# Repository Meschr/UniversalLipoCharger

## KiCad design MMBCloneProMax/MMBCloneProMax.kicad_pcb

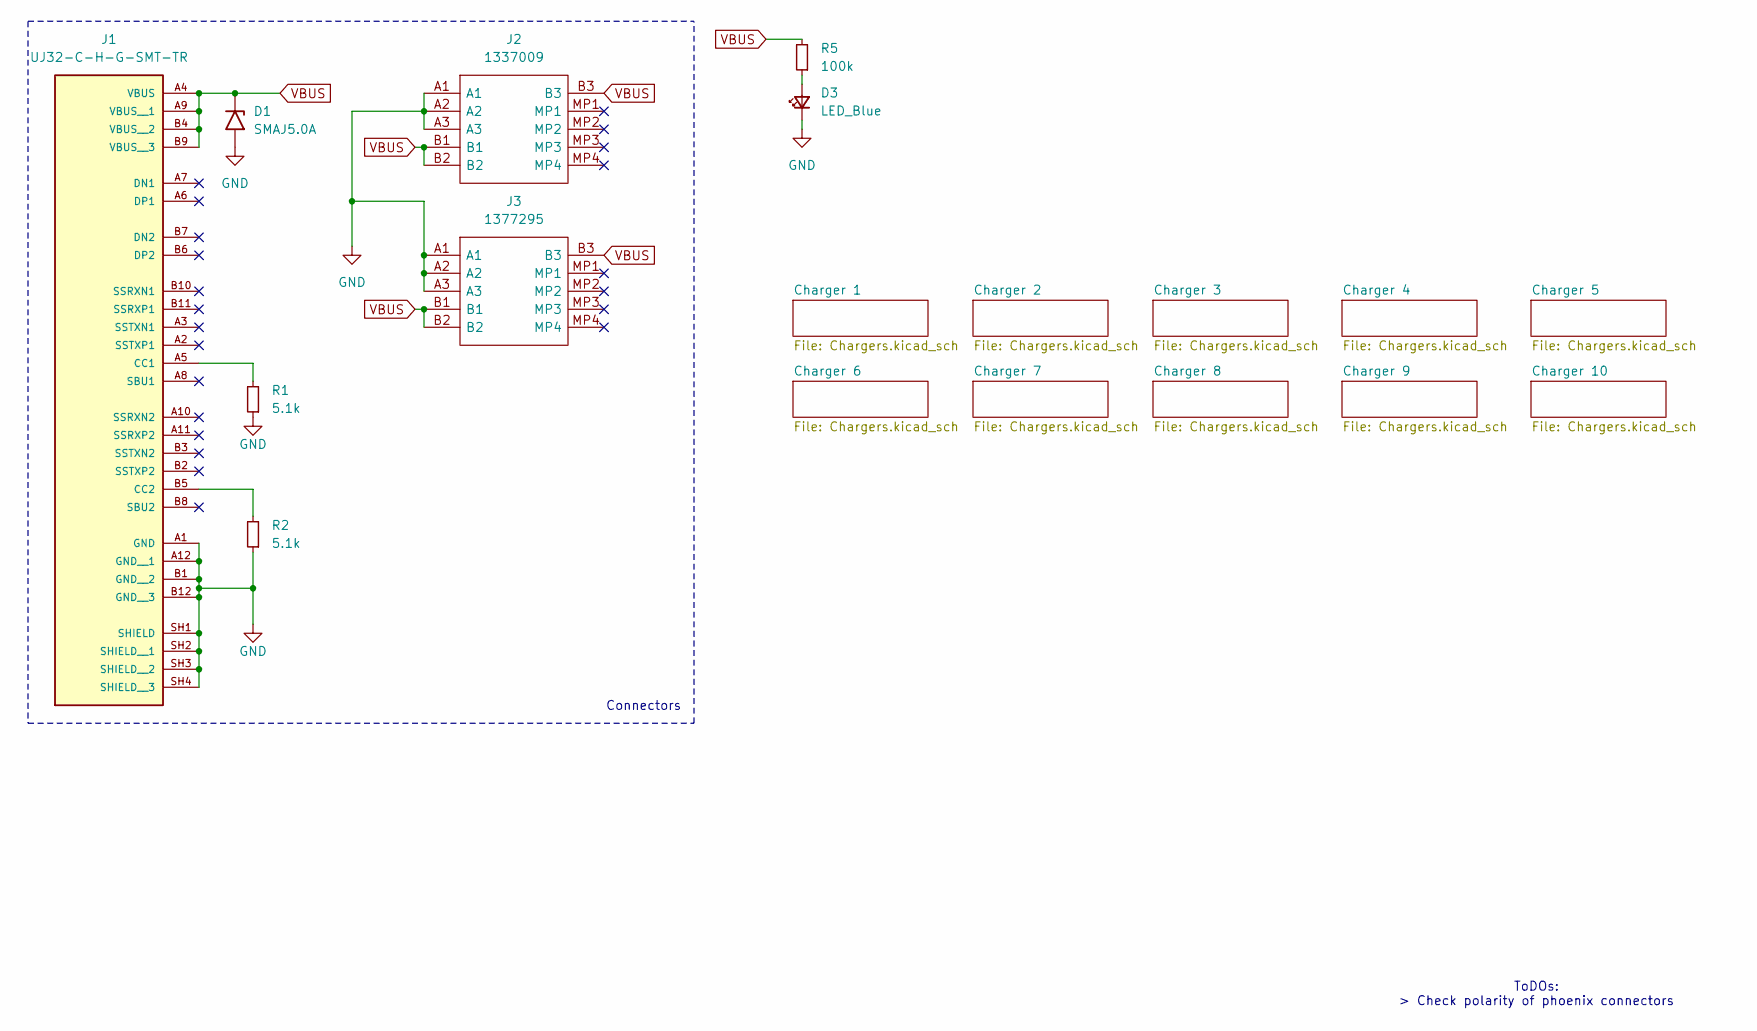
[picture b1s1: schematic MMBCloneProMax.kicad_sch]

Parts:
D1: SMAJ5.0A; D_SMA
D3: LED_Blue; LED_0603_1608Metric
J1: UJ32-C-H-G-SMT-TR; CUI_UJ32-C-H-G-SMT-TR; PARTREV 1.01
J2: 1337009; Mouser Part Number 651-1337009
J3: 1377295; Mouser Part Number 651-1377295
R1, R2: 5.1k; R_0603_1608Metric
R5: 100k; R_0603_1608Metric

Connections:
GND: D1.2 (A2), D3.1 (K), J1.A1 (GND), J1.A12 (GND__1), J1.B1 (GND__2), J1.B12 (GND__3), J1.SH1 (SHIELD), J1.SH2 (SHIELD__1), J1.SH3 (SHIELD__2), J1.SH4 (SHIELD__3), J2.A1, J2.A2, J2.A3, J3.A1, J3.A2, J3.A3, R1.1, R2.1; also elsewhere on the board
unnamed: D3.2 (A), R5.1
unnamed: J1.A5 (CC1), R1.2
unnamed: J1.B5 (CC2), R2.2
VBUS: D1.1 (A1), J1.A4 (VBUS), J1.A9 (VBUS__1), J1.B4 (VBUS__2), J1.B9 (VBUS__3), J2.B1, J2.B2, J2.B3, J3.B1, J3.B2, J3.B3, R5.2; also elsewhere on the board

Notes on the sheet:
Connectors
ToDOs: > Check polarity of phoenix connectors

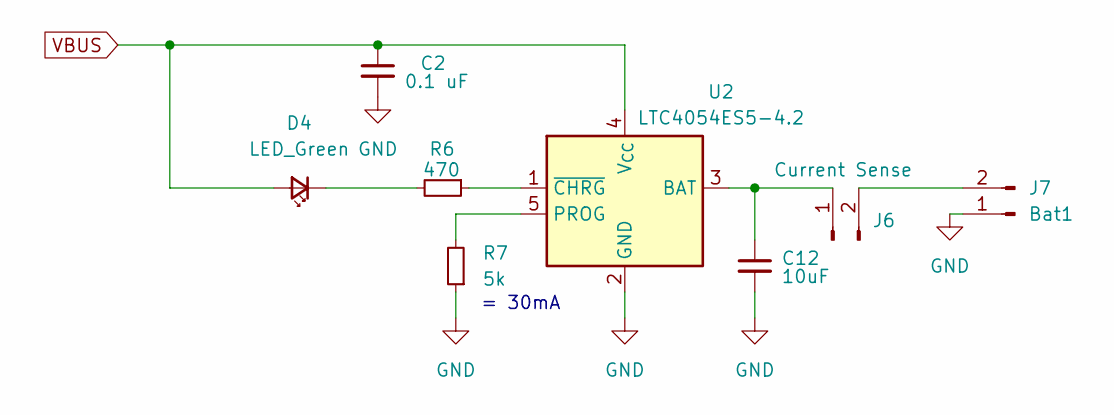
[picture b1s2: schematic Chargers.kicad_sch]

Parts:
C2: 0.1 uF; C_0603_1608Metric
C12: 10uF; C_0603_1608Metric
D4: LED_Green; LED_0603_1608Metric
J6: Current Sense; PinHeader_1x02_P2.54mm_Vertical
J7: Bat1; SHDR2W64P0X254_1X2_508X580X1170P
R6: 470; R_0603_1608Metric
R7: 5k; C_0603_1608Metric
U2: LTC4054ES5-4.2; TSOT-23-5

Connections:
GND: C2.2, C12.2, J7.1, R7.1, U2.2 (GND); also elsewhere on the board
unnamed: D4.1 (K), R6.2
unnamed: C12.1, J6.1, U2.3 (BAT)
unnamed: J6.2, J7.2
unnamed: R7.2, U2.5 (PROG)
unnamed: R6.1, U2.1 (~CHRG)
VBUS: C2.1, D4.2 (A), U2.4 (V_{CC}); also elsewhere on the board

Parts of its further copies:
C1, C3, C4, C5, C6, C7, C8, C9, C10: 0.1 uF; C_0603_1608Metric
C11, C13, C14, C15, C16, C17, C18, C19, C20: 10uF; C_0603_1608Metric
D2, D5, D6, D7, D8, D9, D10, D11, D12: LED_Green; LED_0603_1608Metric
J4, J8, J10, J12, J14, J16, J18, J20, J22: Current Sense; PinHeader_1x02_P2.54mm_Vertical
J5, J9, J11, J13, J15, J17, J19, J21, J23: Bat1; SHDR2W64P0X254_1X2_508X580X1170P
R3, R8, R10, R12, R14, R16, R18, R20, R22: 470; R_0603_1608Metric
R4, R9, R11, R13, R15, R17, R19, R21, R23: 5k; C_0603_1608Metric
U1, U3, U4, U5, U6, U7, U8, U9, U10: LTC4054ES5-4.2; TSOT-23-5

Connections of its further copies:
GND: C1.2, C3.2, C4.2, C5.2, C6.2, C7.2, C8.2, C9.2, C10.2, C11.2, C13.2, C14.2, C15.2, C16.2, C17.2, C18.2, C19.2, C20.2, J5.1, J9.1, J11.1, J13.1, J15.1, J17.1, J19.1, J21.1, J23.1, R4.1, R9.1, R11.1, R13.1, R15.1, R17.1, R19.1, R21.1, R23.1, U1.2 (GND), U3.2 (GND), U4.2 (GND), U5.2 (GND), U6.2 (GND), U7.2 (GND), U8.2 (GND), U9.2 (GND), U10.2 (GND); also elsewhere on the board
unnamed: D2.1 (K), R3.2
unnamed: D5.1 (K), R8.2
unnamed: D6.1 (K), R10.2
unnamed: D7.1 (K), R12.2
unnamed: D8.1 (K), R14.2
unnamed: D9.1 (K), R16.2
unnamed: D10.1 (K), R18.2
unnamed: D11.1 (K), R20.2
unnamed: D12.1 (K), R22.2
unnamed: C11.1, J4.1, U1.3 (BAT)
unnamed: J4.2, J5.2
unnamed: C13.1, J8.1, U3.3 (BAT)
unnamed: J8.2, J9.2
unnamed: C14.1, J10.1, U4.3 (BAT)
unnamed: J10.2, J11.2
unnamed: C15.1, J12.1, U5.3 (BAT)
unnamed: J12.2, J13.2
unnamed: C16.1, J14.1, U6.3 (BAT)
unnamed: J14.2, J15.2
unnamed: C17.1, J16.1, U7.3 (BAT)
unnamed: J16.2, J17.2
unnamed: C18.1, J18.1, U8.3 (BAT)
unnamed: J18.2, J19.2
unnamed: C19.1, J20.1, U9.3 (BAT)
unnamed: J20.2, J21.2
unnamed: C20.1, J22.1, U10.3 (BAT)
unnamed: J22.2, J23.2
unnamed: R4.2, U1.5 (PROG)
unnamed: R3.1, U1.1 (~CHRG)
unnamed: R9.2, U3.5 (PROG)
unnamed: R8.1, U3.1 (~CHRG)
unnamed: R11.2, U4.5 (PROG)
unnamed: R10.1, U4.1 (~CHRG)
unnamed: R13.2, U5.5 (PROG)
unnamed: R12.1, U5.1 (~CHRG)
unnamed: R15.2, U6.5 (PROG)
unnamed: R14.1, U6.1 (~CHRG)
unnamed: R17.2, U7.5 (PROG)
unnamed: R16.1, U7.1 (~CHRG)
unnamed: R19.2, U8.5 (PROG)
unnamed: R18.1, U8.1 (~CHRG)
unnamed: R21.2, U9.5 (PROG)
unnamed: R20.1, U9.1 (~CHRG)
unnamed: R23.2, U10.5 (PROG)
unnamed: R22.1, U10.1 (~CHRG)
VBUS: C1.1, C3.1, C4.1, C5.1, C6.1, C7.1, C8.1, C9.1, C10.1, D2.2 (A), D5.2 (A), D6.2 (A), D7.2 (A), D8.2 (A), D9.2 (A), D10.2 (A), D11.2 (A), D12.2 (A), U1.4 (V_{CC}), U3.4 (V_{CC}), U4.4 (V_{CC}), U5.4 (V_{CC}), U6.4 (V_{CC}), U7.4 (V_{CC}), U8.4 (V_{CC}), U9.4 (V_{CC}), U10.4 (V_{CC}); also elsewhere on the board

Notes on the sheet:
= 30mA

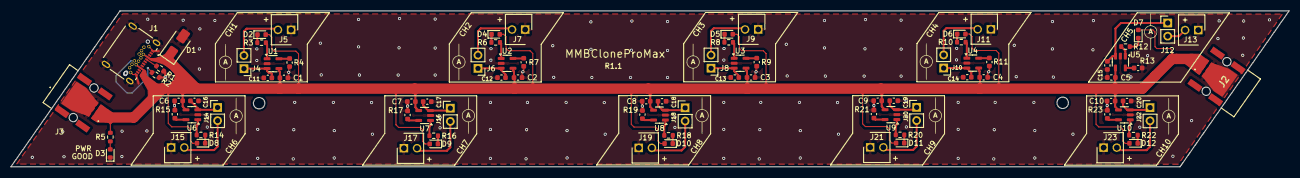
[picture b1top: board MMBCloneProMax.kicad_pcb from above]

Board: 2 copper layers, 246.2 x 30.0 mm, 88 parts (0 on the bottom side), 55 nets.

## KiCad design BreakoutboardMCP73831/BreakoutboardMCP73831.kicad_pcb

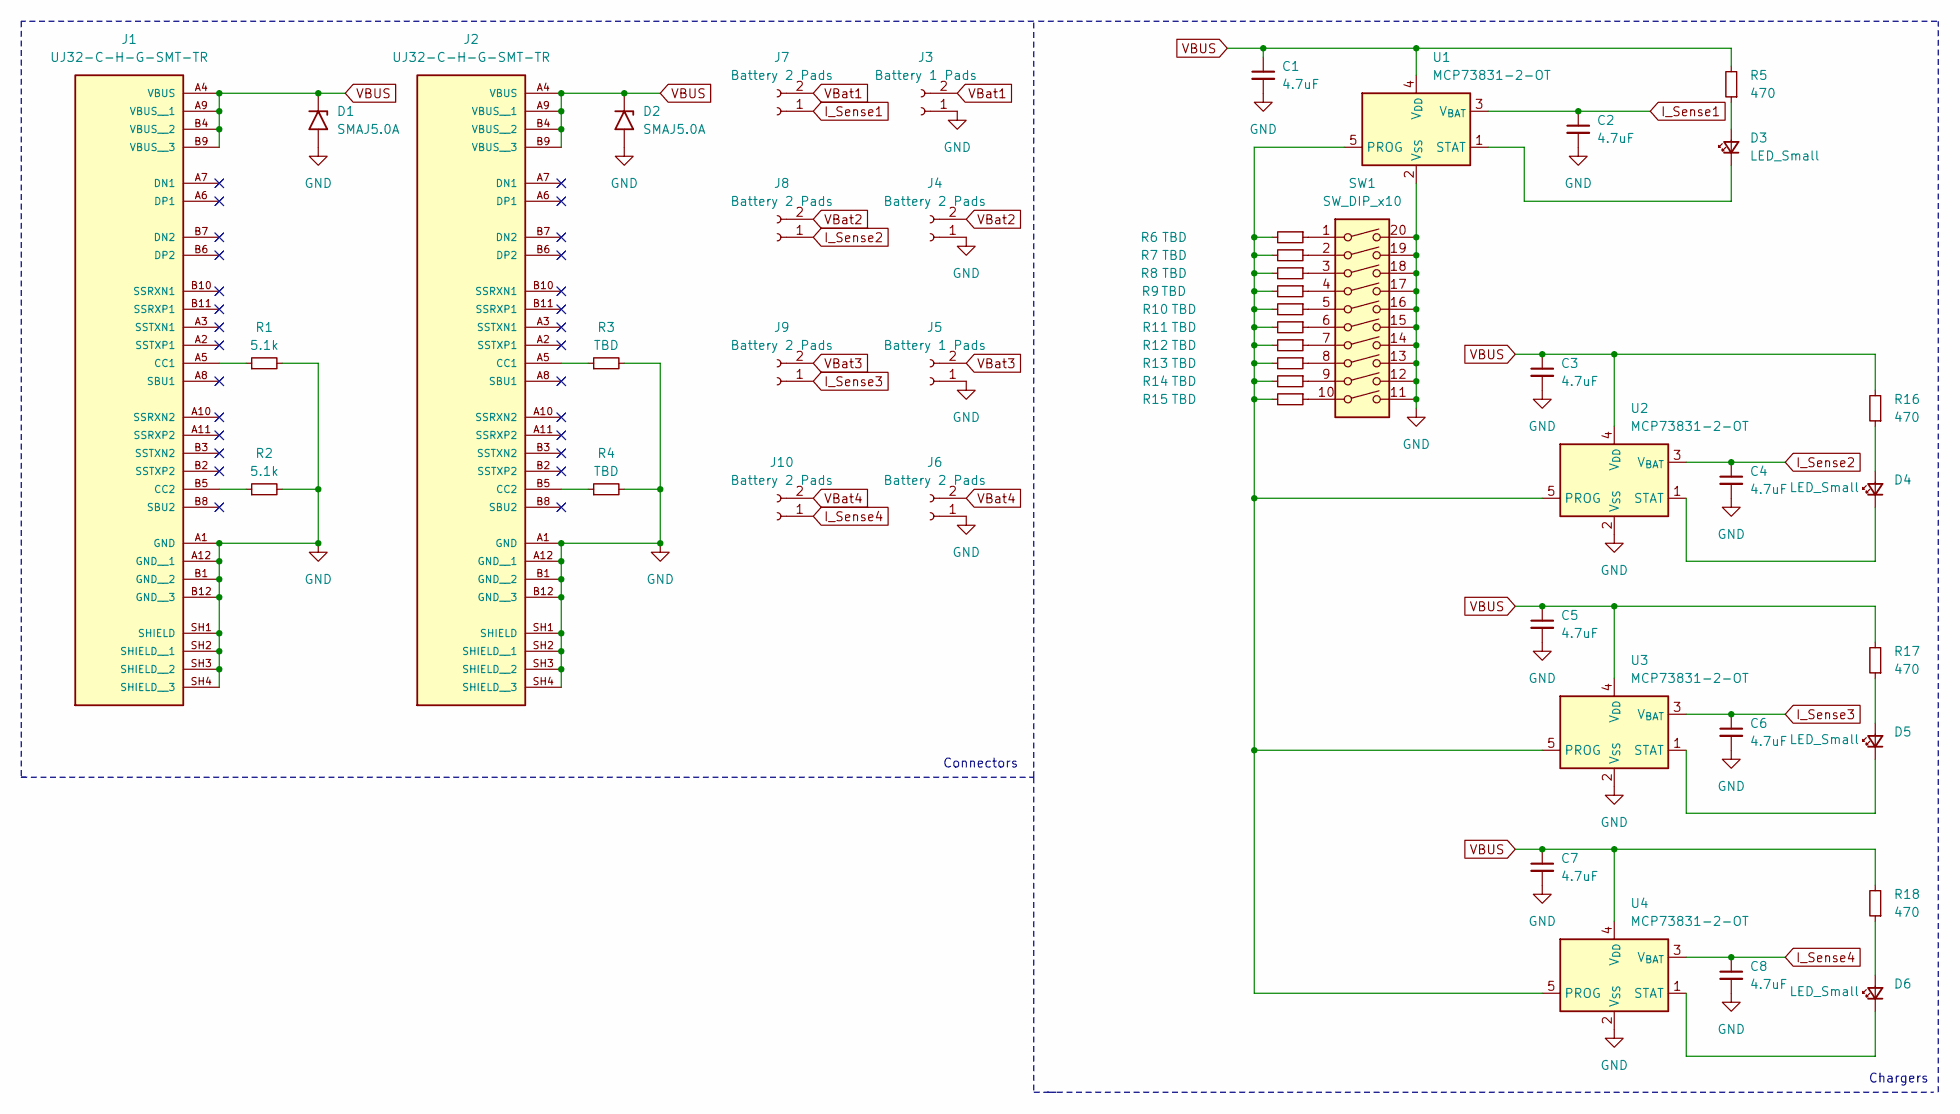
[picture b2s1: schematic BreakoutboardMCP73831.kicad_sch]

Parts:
C1, C2, C3, C4, C5, C6, C7, C8: 4.7uF; C_0402_1005Metric
D1, D2: SMAJ5.0A; D_SMA
D3, D4, D5, D6: LED_Small; LED_0402_1005Metric
J1, J2: UJ32-C-H-G-SMT-TR; CUI_UJ32-C-H-G-SMT-TR; PARTREV 1.01
J3, J5: Battery 1 Pads; PinHeader_1x02_P2.54mm_Vertical
J4, J6, J7, J8, J9, J10: Battery 2 Pads; PinHeader_1x02_P2.54mm_Vertical
R1, R2: 5.1k; R_0402_1005Metric
R3, R4, R6, R7, R8, R9, R10, R11, R12, R13, R14, R15: TBD; R_0402_1005Metric
R5, R16, R17, R18: 470; R_0402_1005Metric
SW1: SW_DIP_x10; SW_DIP_SPSTx10_Slide_6.7x26.96mm_W6.73mm_P2.54mm_LowProfile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
U1, U2, U3, U4: MCP73831-2-OT; SOT-23-5

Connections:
GND: C1.2, C2.2, C3.2, C4.2, C5.2, C6.2, C7.2, C8.2, D1.2 (A2), D2.2 (A2), J1.A1 (GND), J1.A12 (GND__1), J1.B1 (GND__2), J1.B12 (GND__3), J1.SH1 (SHIELD), J1.SH2 (SHIELD__1), J1.SH3 (SHIELD__2), J1.SH4 (SHIELD__3), J2.A1 (GND), J2.A12 (GND__1), J2.B1 (GND__2), J2.B12 (GND__3), J2.SH1 (SHIELD), J2.SH2 (SHIELD__1), J2.SH3 (SHIELD__2), J2.SH4 (SHIELD__3), J3.1, J4.1, J5.1, J6.1, R1.2, R2.2, R3.2, R4.2, SW1.11, SW1.12, SW1.13, SW1.14, SW1.15, SW1.16, SW1.17, SW1.18, SW1.19, SW1.20, U1.2 (V_{SS}), U2.2 (V_{SS}), U3.2 (V_{SS}), U4.2 (V_{SS})
I_Sense1: C2.1, J7.1, U1.3 (V_{BAT})
I_Sense2: C4.1, J8.1, U2.3 (V_{BAT})
I_Sense3: C6.1, J9.1, U3.3 (V_{BAT})
I_Sense4: C8.1, J10.1, U4.3 (V_{BAT})
unnamed: D3.2 (A), R5.1
unnamed: D3.1 (K), U1.1 (STAT)
unnamed: D4.2 (A), R16.1
unnamed: D4.1 (K), U2.1 (STAT)
unnamed: D5.2 (A), R17.1
unnamed: D5.1 (K), U3.1 (STAT)
unnamed: D6.2 (A), R18.1
unnamed: D6.1 (K), U4.1 (STAT)
unnamed: J1.A5 (CC1), R1.1
unnamed: J1.B5 (CC2), R2.1
unnamed: J2.A5 (CC1), R3.1
unnamed: J2.B5 (CC2), R4.1
unnamed: R6.1, SW1.1
unnamed: R7.1, SW1.2
unnamed: R8.1, SW1.3
unnamed: R9.1, SW1.4
unnamed: R10.1, SW1.5
unnamed: R11.1, SW1.6
unnamed: R12.1, SW1.7
unnamed: R13.1, SW1.8
unnamed: R14.1, SW1.9
unnamed: R15.1, SW1.10
unnamed: R6.2, R7.2, R8.2, R9.2, R10.2, R11.2, R12.2, R13.2, R14.2, R15.2, U1.5 (PROG), U2.5 (PROG), U3.5 (PROG), U4.5 (PROG)
VBUS: C1.1, C3.1, C5.1, C7.1, D1.1 (A1), D2.1 (A1), J1.A4 (VBUS), J1.A9 (VBUS__1), J1.B4 (VBUS__2), J1.B9 (VBUS__3), J2.A4 (VBUS), J2.A9 (VBUS__1), J2.B4 (VBUS__2), J2.B9 (VBUS__3), R5.2, R16.2, R17.2, R18.2, U1.4 (V_{DD}), U2.4 (V_{DD}), U3.4 (V_{DD}), U4.4 (V_{DD})
VBat1: J3.2, J7.2
VBat2: J4.2, J8.2
VBat3: J5.2, J9.2
VBat4: J6.2, J10.2

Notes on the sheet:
Chargers
Connectors

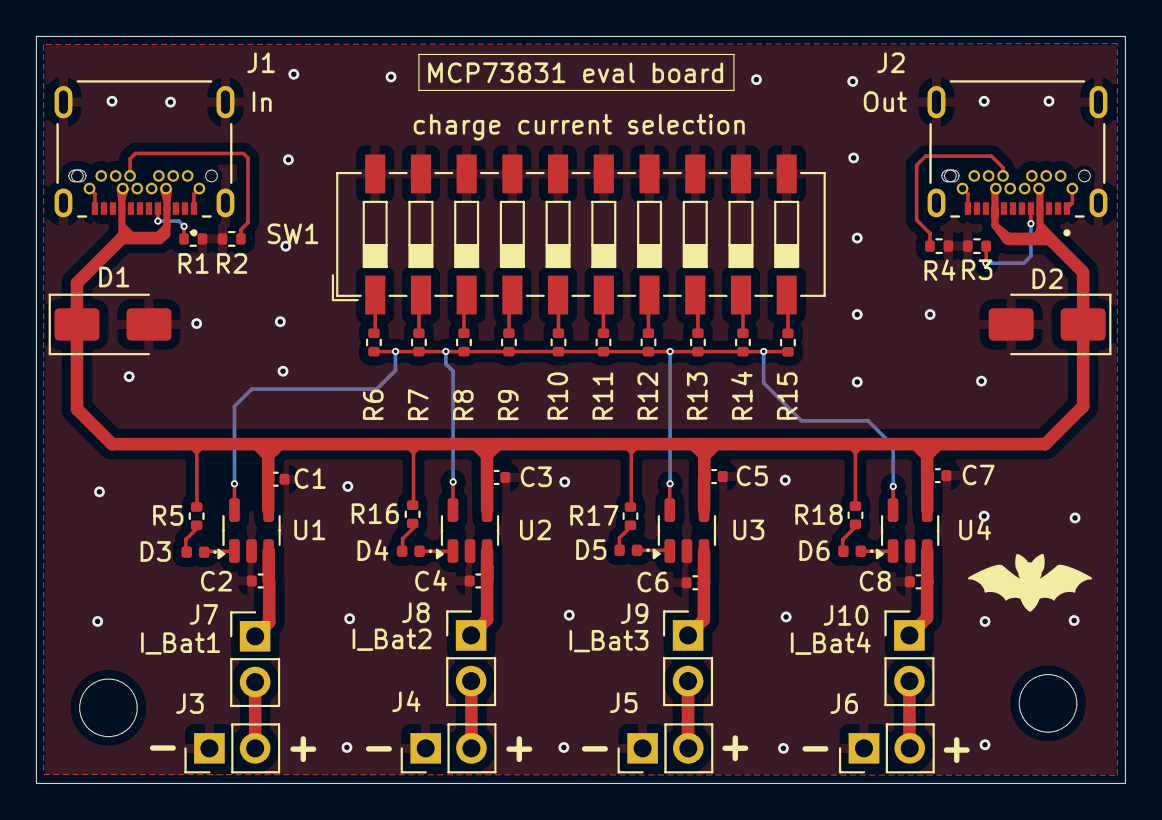
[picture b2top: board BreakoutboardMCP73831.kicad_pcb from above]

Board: 2 copper layers, 60.5 x 41.5 mm, 47 parts (0 on the bottom side), 33 nets.

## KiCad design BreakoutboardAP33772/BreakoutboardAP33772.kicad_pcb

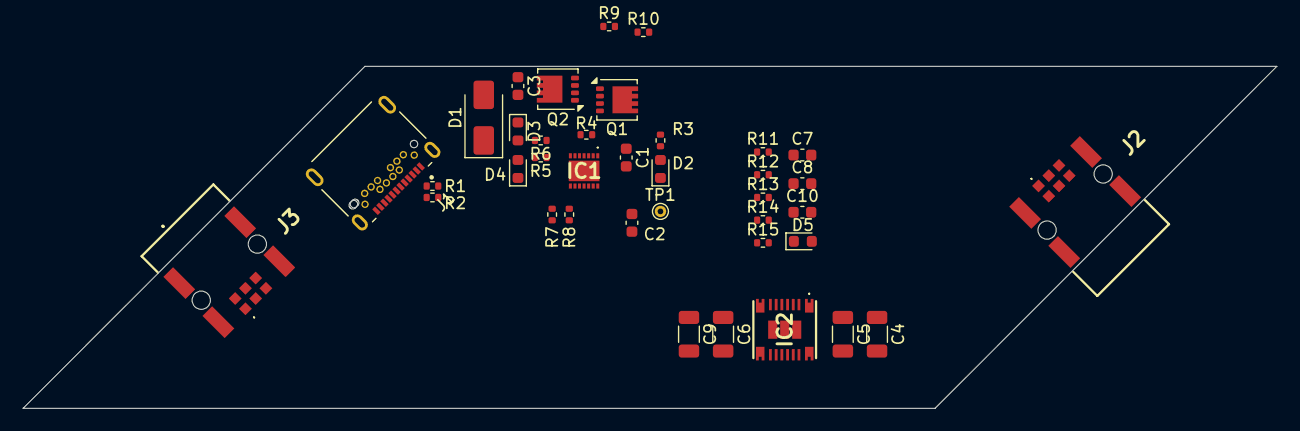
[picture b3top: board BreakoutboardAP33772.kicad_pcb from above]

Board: 2 copper layers, 110.0 x 30.0 mm, 38 parts (0 on the bottom side), 28 nets, no tracks yet.

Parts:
C1, C2, C3: 10uF; C_0603_1608Metric
C4, C5: 22uF; C_1206_3216Metric
C6, C9: 10uF; C_1206_3216Metric
C7: 0.1uF; C_0603_1608Metric
C8: 47pF; C_0603_1608Metric
C10: 22nF; C_0603_1608Metric
D1: SMAJ5.0A; D_SMA
D2, D3, D4, D5: LED_Blue; LED_0603_1608Metric
IC1: AP33771CFBZ-13-FA01; AP33771CFBZ13FA01
IC2: TPSM86638RCGR
J1: UJ32-C-H-G-SMT-TR; CUI_UJ32-C-H-G-SMT-TR
J2: 1337009
J3: 1377295
Q1, Q2: DMN3008SFG; Diodes_PowerDI3333-8
R1, R2: 5.1k; R_0402_1005Metric
R3, R4: 100k; R_0402_1005Metric
R5, R6: 1k; R_0402_1005Metric
R7, R8: TBD; R_0402_1005Metric
R9: 10; R_0402_1005Metric
R10: 100; R_0402_1005Metric
R11: 73.3k; R_0402_1005Metric
R12: 0; R_0402_1005Metric
R13, R14, R15: 10k; R_0402_1005Metric
TP1: 5V; TestPoint_THTPad_D1.0mm_Drill0.5mm

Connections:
5V: C4.1, C5.1, C7.1, IC2.1 (VOUT_1), IC2.16 (VOUT_2), IC2.20 (VOUT_3), IC2.21 (VOUT_4), IC2.26 (VOUT_5), IC2.27 (VOUT_6), R11.1, R12.1
CC1: IC1.11 (CC1), J1.A5 (CC1), R1.2
CC2: IC1.10 (CC2), J1.B5 (CC2), R2.2
DN: IC1.12 (DN), J1.A7 (DN1), J1.B7 (DN2)
DP: IC1.13 (DP), J1.A6 (DP1), J1.B6 (DP2)
FB: C8.1, IC2.4 (FB), R11.2, R13.2
GND: C1.2, C2.2, C3.2, C4.2, C5.2, C6.2, C7.2, C9.2, C10.1, D1.2 (A2), D2.1 (K), D3.1 (K), D4.1 (K), IC1.5 (GND), IC1.15 (EP), IC2.5 (AGND), IC2.13 (NC_1), IC2.14 (NC_2), IC2.15 (NC_3), IC2.17 (PGND_1), IC2.18 (PGND_2), IC2.19 (PGND_3), R1.1, R2.1, R7.2, R8.1, R13.1, R14.2
unnamed: C8.2, R12.2
unnamed: D2.2 (A), R3.1
unnamed: D3.2 (A), R6.2
unnamed: D4.2 (A), R5.2
unnamed: D5.1 (K), R15.2
unnamed: IC1.6 (FLIP), R6.1
unnamed: IC1.9 (ISEL), R8.2
unnamed: IC1.7 (LED), R5.1
unnamed: IC1.2 (PWR_EN), R9.2
unnamed: C2.1, IC1.14 (V5V), TP1.1
unnamed: IC1.3 (VCC), Q1.1 (S), Q1.2 (S), Q1.3 (S), R4.2
unnamed: IC1.1 (VOUT), R10.2
unnamed: IC1.8 (VSEL), R7.1
unnamed: IC2.2 (MODE), R14.1
unnamed: IC2.6 (PG), R15.1
unnamed: C10.2, IC2.7 (SS)
unnamed: J1.A1 (GND), J1.A12 (GND__1), J1.B1 (GND__2), J1.B12 (GND__3), J1.SH1 (SHIELD), J1.SH2 (SHIELD__1), J1.SH3 (SHIELD__2), J1.SH4 (SHIELD__3)
unnamed: Q1.5 (D), Q2.5 (D)
unnamed: Q1.4 (G), Q2.4 (G), R9.1
VBUS: C1.1, D1.1 (A1), IC1.4 (ISENP), J1.A4 (VBUS), J1.A9 (VBUS__1), J1.B4 (VBUS__2), J1.B9 (VBUS__3), R3.2, R4.1
VIN: C3.1, C6.1, C9.1, D5.2 (A), IC2.8 (VIN_1), IC2.9 (VIN_2), IC2.22 (VIN_3), IC2.23 (VIN_4), IC2.24 (VIN_5), IC2.25 (VIN_6), Q2.1 (S), Q2.2 (S), Q2.3 (S), R10.1

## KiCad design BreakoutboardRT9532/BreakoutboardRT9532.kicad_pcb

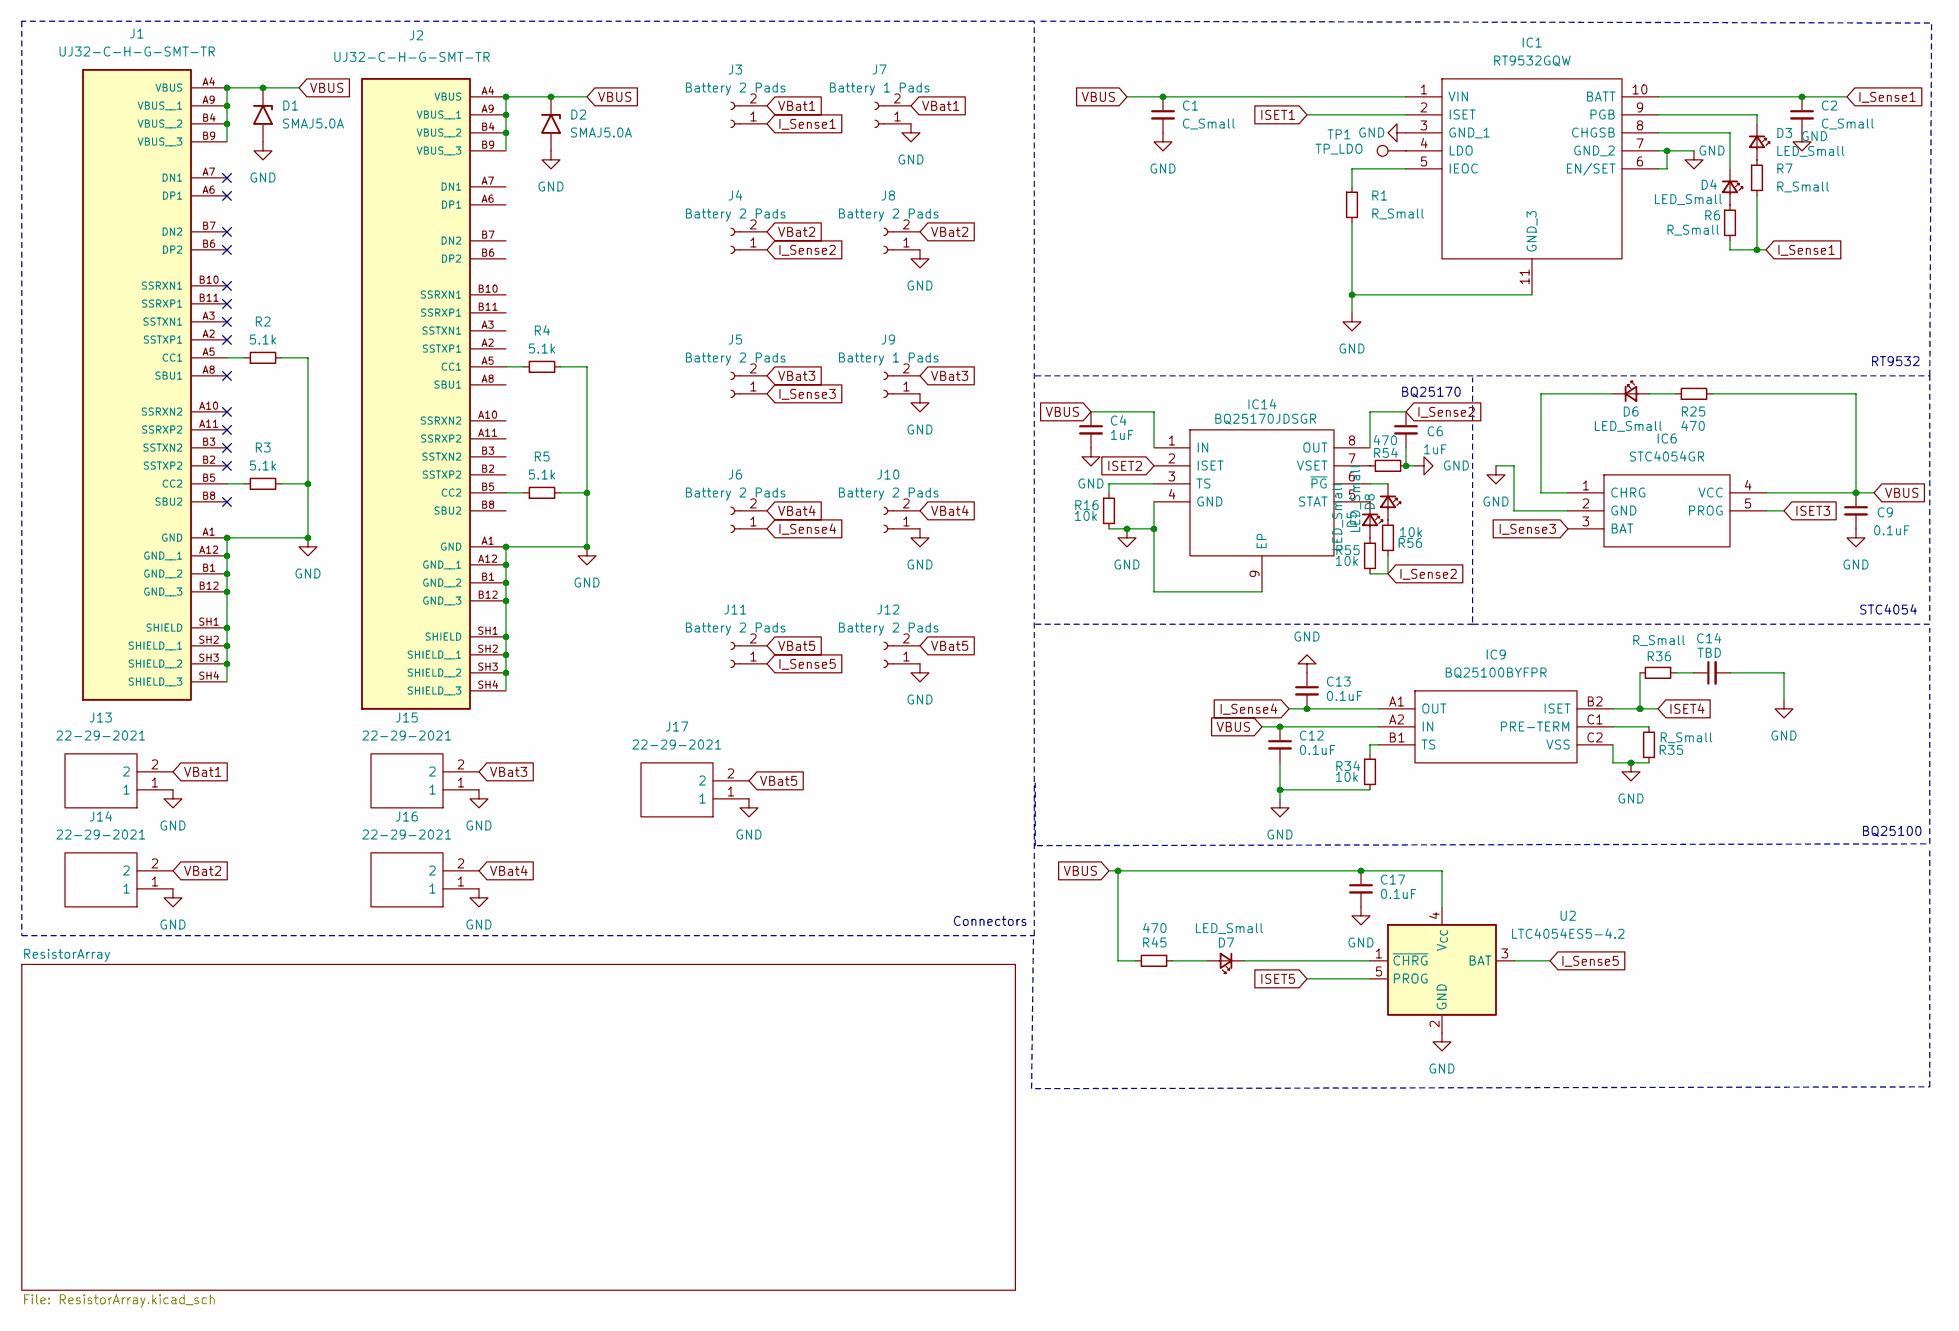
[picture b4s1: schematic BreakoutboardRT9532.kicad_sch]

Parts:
C1, C2: C_Small; C_0603_1608Metric_Pad1.08x0.95mm_HandSolder
C4, C6: 1uF; C_0603_1608Metric_Pad1.08x0.95mm_HandSolder
C9, C12, C13, C17: 0.1uF; C_0603_1608Metric_Pad1.08x0.95mm_HandSolder
C14: TBD; C_0603_1608Metric_Pad1.08x0.95mm_HandSolder
D1, D2: SMAJ5.0A; D_SMA
D3, D4, D5, D6, D7, D8: LED_Small; LED_0603_1608Metric
IC1: RT9532GQW; SON50P200X300X80-11N; Manufacturer_Part_Number RT9532GQW
IC6: STC4054GR; SOT95P280X110-5N; Mouser Part Number 511-STC4054GR
IC9: BQ25100BYFPR; BGA6C40P2X3_88X158X50; Mouser Part Number 595-BQ25100BYFPR
IC14: BQ25170JDSGR; SON50P200X200X80-9N; Mouser Part Number 595-BQ25170JDSGR
J1, J2: UJ32-C-H-G-SMT-TR; CUI_UJ32-C-H-G-SMT-TR; PARTREV 1.01
J3, J4, J5, J6, J8, J10, J11, J12: Battery 2 Pads; PinHeader_1x02_P2.54mm_Vertical
J7, J9: Battery 1 Pads; PinHeader_1x02_P2.54mm_Vertical
J13, J14, J15, J16, J17: 22-29-2021; SHDR2W64P0X254_1X2_508X580X1170P; Mouser Part Number 538-22-29-2021
R1: R_Small; R_0603_1608Metric
R2, R3, R4, R5: 5.1k; R_0603_1608Metric
R6, R7, R35, R36: R_Small; C_0603_1608Metric
R16, R34, R55, R56: 10k; C_0603_1608Metric
R25, R45, R54: 470; R_0603_1608Metric
TP1: TP_LDO; TestPoint_Pad_1.0x1.0mm
U2: LTC4054ES5-4.2; TSOT-23-5

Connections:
GND: C1.2, C2.2, C4.2, C6.2, C9.2, C12.2, C13.1, C14.2, C17.2, D1.2 (A2), D2.2 (A2), IC1.3 (GND_1), IC1.6 (EN/SET), IC1.7 (GND_2), IC1.11 (GND_3), IC6.2 (GND), IC9.C2 (VSS), IC14.4 (GND), IC14.9 (EP), J1.A1 (GND), J1.A12 (GND__1), J1.B1 (GND__2), J1.B12 (GND__3), J1.SH1 (SHIELD), J1.SH2 (SHIELD__1), J1.SH3 (SHIELD__2), J1.SH4 (SHIELD__3), J2.A1 (GND), J2.A12 (GND__1), J2.B1 (GND__2), J2.B12 (GND__3), J2.SH1 (SHIELD), J2.SH2 (SHIELD__1), J2.SH3 (SHIELD__2), J2.SH4 (SHIELD__3), J7.1, J8.1, J9.1, J10.1, J12.1, J13.1, J14.1, J15.1, J16.1, J17.1, R1.2, R2.2, R3.2, R4.2, R5.2, R16.2, R34.2, R35.1, R54.2, U2.2 (GND); also elsewhere on the board
ISET1: IC1.2 (ISET); also elsewhere on the board
ISET2: IC14.2 (ISET); also elsewhere on the board
ISET3: IC6.5 (PROG); also elsewhere on the board
ISET4: IC9.B2 (ISET), R36.2; also elsewhere on the board
ISET5: U2.5 (PROG); also elsewhere on the board
I_Sense1: C2.1, IC1.10 (BATT), J3.1, R6.2, R7.2
I_Sense2: C6.1, IC14.8 (OUT), J4.1, R55.2, R56.1
I_Sense3: IC6.3 (BAT), J5.1
I_Sense4: C13.2, IC9.A1 (OUT), J6.1
I_Sense5: J11.1, U2.3 (BAT)
unnamed: C14.1, R36.1
unnamed: D3.2 (A), R7.1
unnamed: D3.1 (K), IC1.9 (PGB)
unnamed: D4.2 (A), R6.1
unnamed: D4.1 (K), IC1.8 (CHGSB)
unnamed: D5.2 (A), R55.1
unnamed: D5.1 (K), IC14.5 (STAT)
unnamed: D6.2 (A), R25.1
unnamed: D6.1 (K), IC6.1 (CHRG)
unnamed: D7.2 (A), R45.1
unnamed: D7.1 (K), U2.1 (~CHRG)
unnamed: D8.2 (A), R56.2
unnamed: D8.1 (K), IC14.6 (~PG)
unnamed: IC1.5 (IEOC), R1.1
unnamed: IC1.4 (LDO), TP1.1
unnamed: IC9.C1 (PRE-TERM), R35.2
unnamed: IC9.B1 (TS), R34.1
unnamed: IC14.3 (TS), R16.1
unnamed: IC14.7 (VSET), R54.1
unnamed: J1.A5 (CC1), R2.1
unnamed: J1.B5 (CC2), R3.1
unnamed: J2.A5 (CC1), R4.1
unnamed: J2.B5 (CC2), R5.1
VBUS: C1.1, C4.1, C9.1, C12.1, C17.1, D1.1 (A1), D2.1 (A1), IC1.1 (VIN), IC6.4 (VCC), IC9.A2 (IN), IC14.1 (IN), J1.A4 (VBUS), J1.A9 (VBUS__1), J1.B4 (VBUS__2), J1.B9 (VBUS__3), J2.A4 (VBUS), J2.A9 (VBUS__1), J2.B4 (VBUS__2), J2.B9 (VBUS__3), R25.2, R45.2, U2.4 (V_{CC}); also elsewhere on the board
VBat1: J3.2, J7.2, J13.2
VBat2: J4.2, J8.2, J14.2
VBat3: J5.2, J9.2, J15.2
VBat4: J6.2, J10.2, J16.2
VBat5: J11.2, J12.2, J17.2

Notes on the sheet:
STC4054
RT9532
BQ25100
Connectors
BQ25170

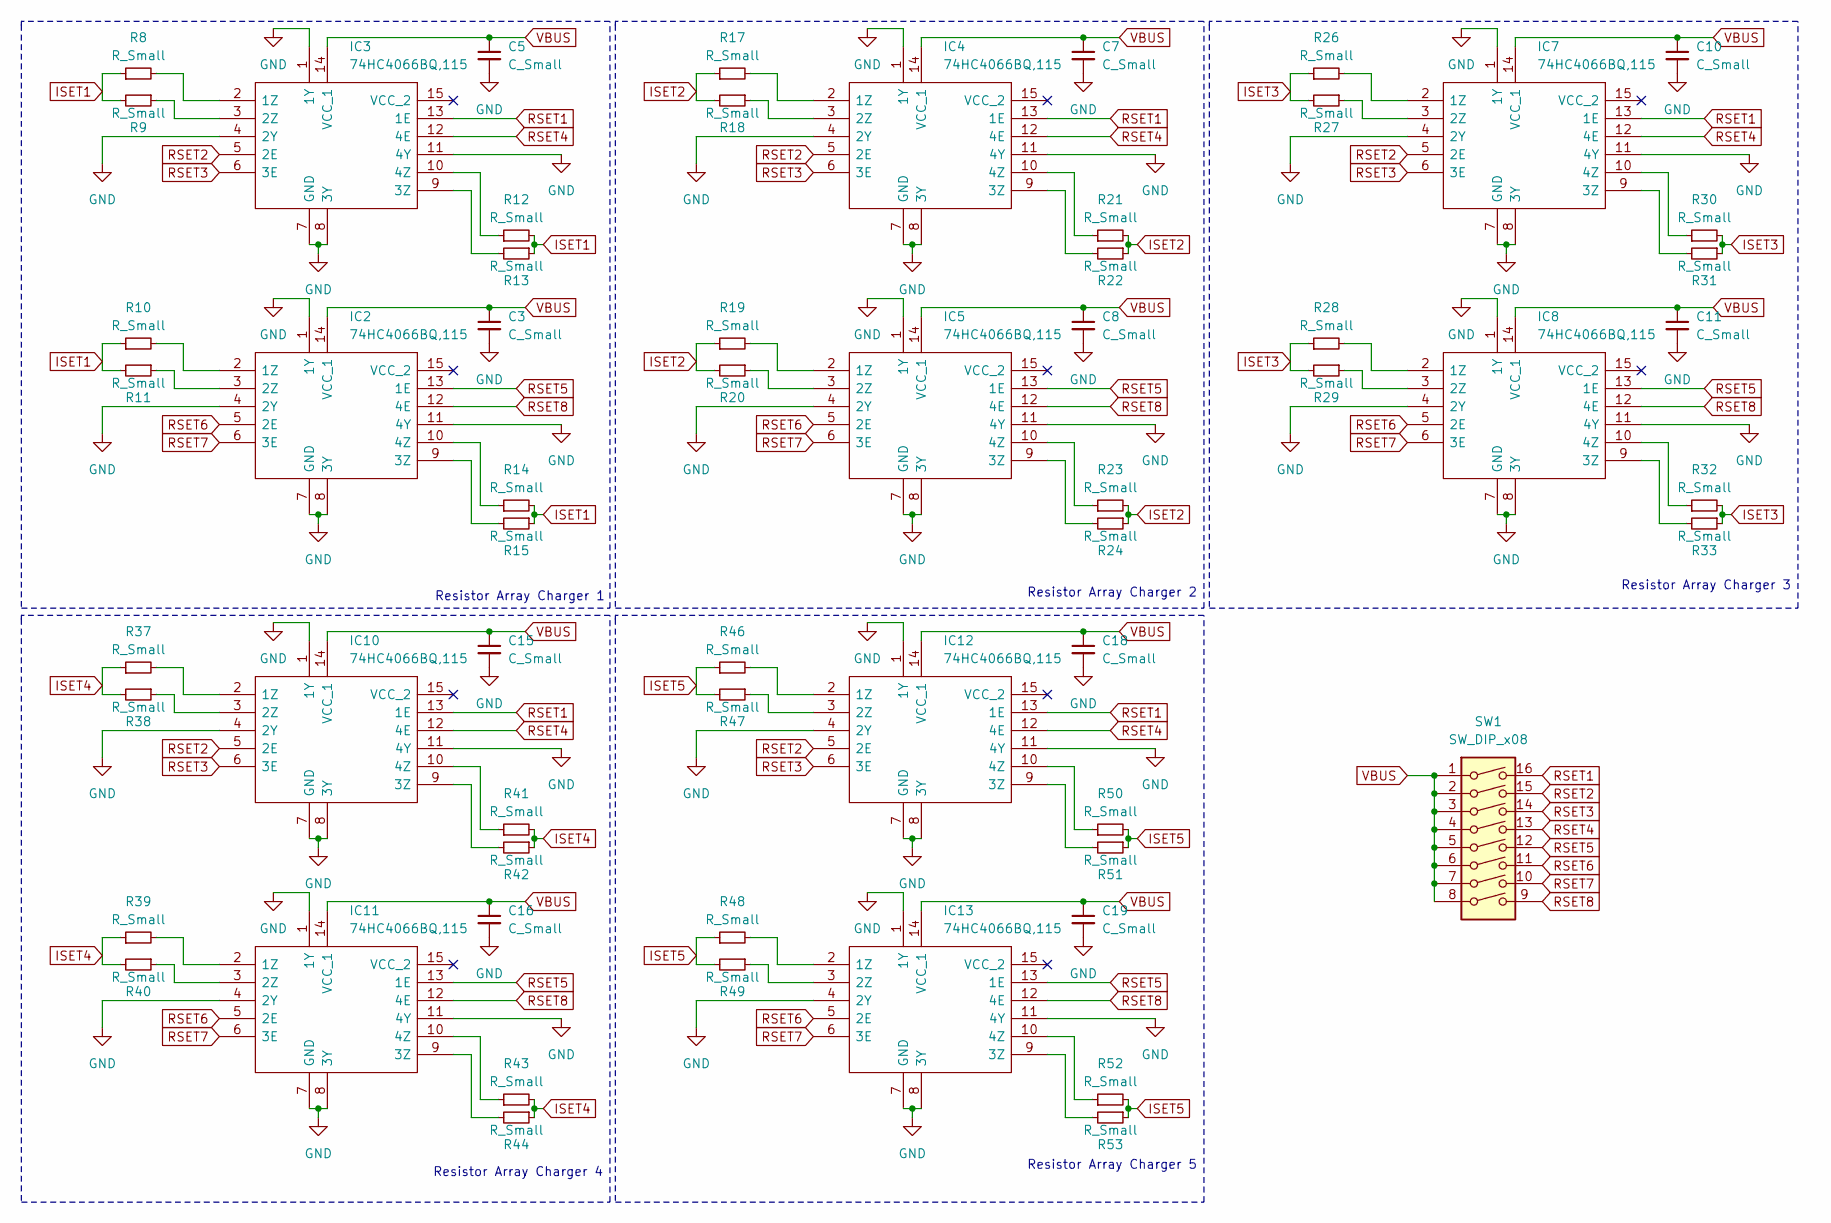
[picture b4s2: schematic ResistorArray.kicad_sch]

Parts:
C3, C5, C7, C8, C10, C11, C15, C16, C18, C19: C_Small; C_0603_1608Metric_Pad1.08x0.95mm_HandSolder
IC2, IC3, IC4, IC5, IC7, IC8, IC10, IC11, IC12, IC13: 74HC4066BQ,115; 74HC4066BQ115; Mouser Part Number 771-HC4066BQ115
R8, R9, R10, R11, R12, R13, R14, R15, R17, R18, R19, R20, R21, R22, R23, R24, R26, R27, R28, R29, R30, R31, R32, R33, R37, R38, R39, R40, R41, R42, R43, R44, R46, R47, R48, R49, R50, R51, R52, R53: R_Small; C_0603_1608Metric
SW1: SW_DIP_x08; ADF08ST04

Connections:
GND: C3.2, C5.2, C7.2, C8.2, C10.2, C11.2, C15.2, C16.2, C18.2, C19.2, IC2.1 (1Y), IC2.4 (2Y), IC2.7 (GND), IC2.8 (3Y), IC2.11 (4Y), IC3.1 (1Y), IC3.4 (2Y), IC3.7 (GND), IC3.8 (3Y), IC3.11 (4Y), IC4.1 (1Y), IC4.4 (2Y), IC4.7 (GND), IC4.8 (3Y), IC4.11 (4Y), IC5.1 (1Y), IC5.4 (2Y), IC5.7 (GND), IC5.8 (3Y), IC5.11 (4Y), IC7.1 (1Y), IC7.4 (2Y), IC7.7 (GND), IC7.8 (3Y), IC7.11 (4Y), IC8.1 (1Y), IC8.4 (2Y), IC8.7 (GND), IC8.8 (3Y), IC8.11 (4Y), IC10.1 (1Y), IC10.4 (2Y), IC10.7 (GND), IC10.8 (3Y), IC10.11 (4Y), IC11.1 (1Y), IC11.4 (2Y), IC11.7 (GND), IC11.8 (3Y), IC11.11 (4Y), IC12.1 (1Y), IC12.4 (2Y), IC12.7 (GND), IC12.8 (3Y), IC12.11 (4Y), IC13.1 (1Y), IC13.4 (2Y), IC13.7 (GND), IC13.8 (3Y), IC13.11 (4Y); also elsewhere on the board
ISET1: R8.1, R9.2, R10.1, R11.2, R12.2, R13.1, R14.2, R15.1; also elsewhere on the board
ISET2: R17.1, R18.2, R19.1, R20.2, R21.2, R22.1, R23.2, R24.1; also elsewhere on the board
ISET3: R26.1, R27.2, R28.1, R29.2, R30.2, R31.1, R32.2, R33.1; also elsewhere on the board
ISET4: R37.1, R38.2, R39.1, R40.2, R41.2, R42.1, R43.2, R44.1; also elsewhere on the board
ISET5: R46.1, R47.2, R48.1, R49.2, R50.2, R51.1, R52.2, R53.1; also elsewhere on the board
unnamed: IC2.2 (1Z), R10.2
unnamed: IC2.3 (2Z), R11.1
unnamed: IC2.9 (3Z), R15.2
unnamed: IC2.10 (4Z), R14.1
unnamed: IC3.2 (1Z), R8.2
unnamed: IC3.3 (2Z), R9.1
unnamed: IC3.9 (3Z), R13.2
unnamed: IC3.10 (4Z), R12.1
unnamed: IC4.2 (1Z), R17.2
unnamed: IC4.3 (2Z), R18.1
unnamed: IC4.9 (3Z), R22.2
unnamed: IC4.10 (4Z), R21.1
unnamed: IC5.2 (1Z), R19.2
unnamed: IC5.3 (2Z), R20.1
unnamed: IC5.9 (3Z), R24.2
unnamed: IC5.10 (4Z), R23.1
unnamed: IC7.2 (1Z), R26.2
unnamed: IC7.3 (2Z), R27.1
unnamed: IC7.9 (3Z), R31.2
unnamed: IC7.10 (4Z), R30.1
unnamed: IC8.2 (1Z), R28.2
unnamed: IC8.3 (2Z), R29.1
unnamed: IC8.9 (3Z), R33.2
unnamed: IC8.10 (4Z), R32.1
unnamed: IC10.2 (1Z), R37.2
unnamed: IC10.3 (2Z), R38.1
unnamed: IC10.9 (3Z), R42.2
unnamed: IC10.10 (4Z), R41.1
unnamed: IC11.2 (1Z), R39.2
unnamed: IC11.3 (2Z), R40.1
unnamed: IC11.9 (3Z), R44.2
unnamed: IC11.10 (4Z), R43.1
unnamed: IC12.2 (1Z), R46.2
unnamed: IC12.3 (2Z), R47.1
unnamed: IC12.9 (3Z), R51.2
unnamed: IC12.10 (4Z), R50.1
unnamed: IC13.2 (1Z), R48.2
unnamed: IC13.3 (2Z), R49.1
unnamed: IC13.9 (3Z), R53.2
unnamed: IC13.10 (4Z), R52.1
RSET1: IC3.13 (1E), IC4.13 (1E), IC7.13 (1E), IC10.13 (1E), IC12.13 (1E), SW1.16
RSET2: IC3.5 (2E), IC4.5 (2E), IC7.5 (2E), IC10.5 (2E), IC12.5 (2E), SW1.15
RSET3: IC3.6 (3E), IC4.6 (3E), IC7.6 (3E), IC10.6 (3E), IC12.6 (3E), SW1.14
RSET4: IC3.12 (4E), IC4.12 (4E), IC7.12 (4E), IC10.12 (4E), IC12.12 (4E), SW1.13
RSET5: IC2.13 (1E), IC5.13 (1E), IC8.13 (1E), IC11.13 (1E), IC13.13 (1E), SW1.12
RSET6: IC2.5 (2E), IC5.5 (2E), IC8.5 (2E), IC11.5 (2E), IC13.5 (2E), SW1.11
RSET7: IC2.6 (3E), IC5.6 (3E), IC8.6 (3E), IC11.6 (3E), IC13.6 (3E), SW1.10
RSET8: IC2.12 (4E), IC5.12 (4E), IC8.12 (4E), IC11.12 (4E), IC13.12 (4E), SW1.9
VBUS: C3.1, C5.1, C7.1, C8.1, C10.1, C11.1, C15.1, C16.1, C18.1, C19.1, IC2.14 (VCC_1), IC3.14 (VCC_1), IC4.14 (VCC_1), IC5.14 (VCC_1), IC7.14 (VCC_1), IC8.14 (VCC_1), IC10.14 (VCC_1), IC11.14 (VCC_1), IC12.14 (VCC_1), IC13.14 (VCC_1), SW1.1, SW1.2, SW1.3, SW1.4, SW1.5, SW1.6, SW1.7, SW1.8; also elsewhere on the board

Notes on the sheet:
Resistor Array Charger 1
Resistor Array Charger 4
Resistor Array Charger 2
Resistor Array Charger 5
Resistor Array Charger 3

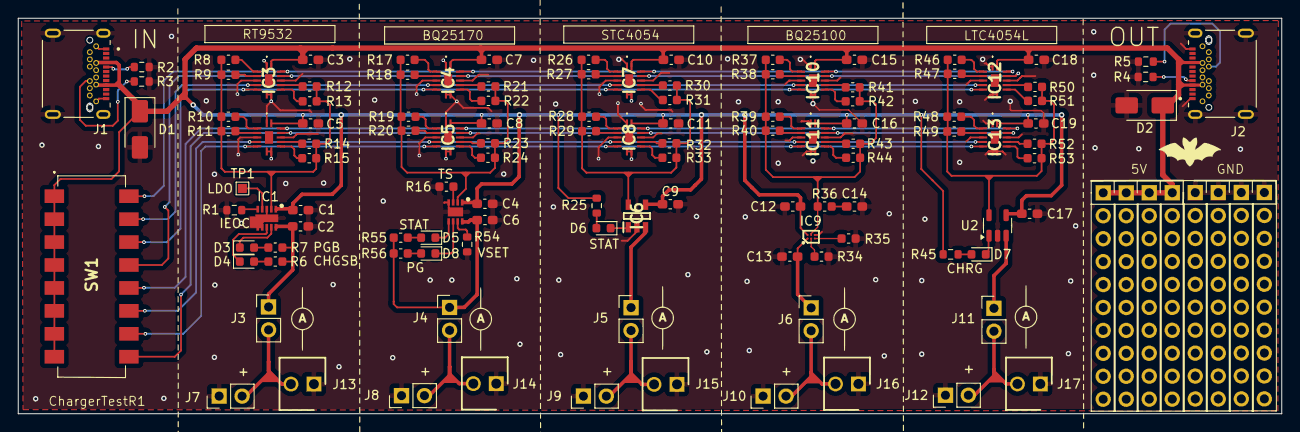
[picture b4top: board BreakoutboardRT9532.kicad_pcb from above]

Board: 2 copper layers, 139.9 x 43.8 mm, 117 parts (0 on the bottom side), 88 nets.

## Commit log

2025-02-01 init
2025-02-05 drc done
2025-10-03 intermediate
